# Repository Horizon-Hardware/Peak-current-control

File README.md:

# Peak-current-control
峰值电流控制PCB和代码

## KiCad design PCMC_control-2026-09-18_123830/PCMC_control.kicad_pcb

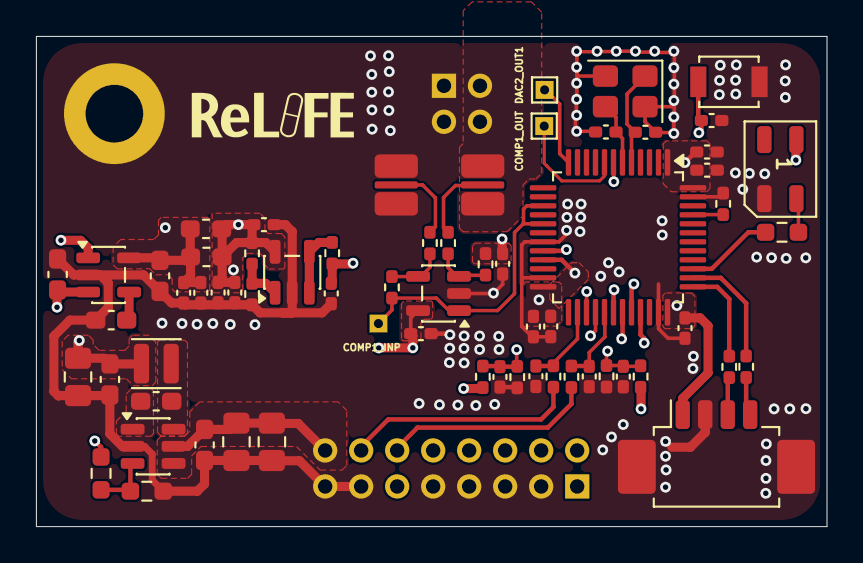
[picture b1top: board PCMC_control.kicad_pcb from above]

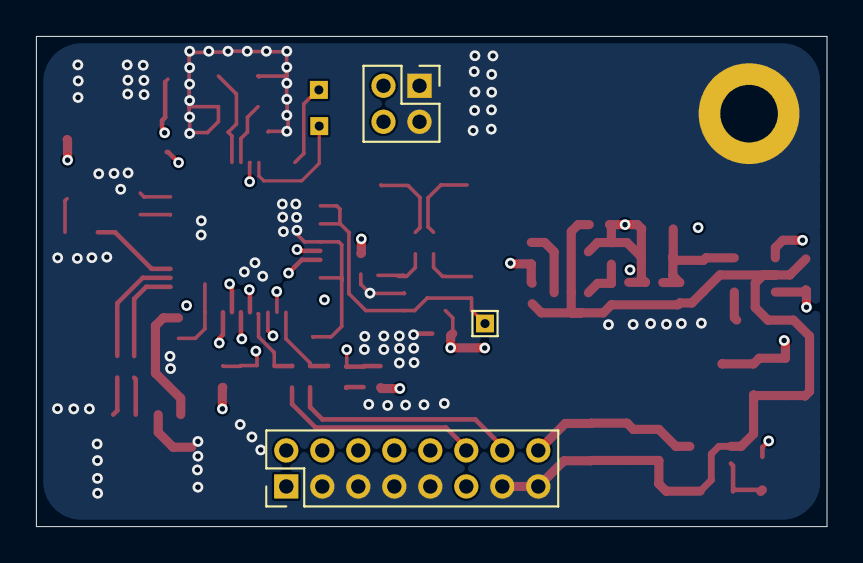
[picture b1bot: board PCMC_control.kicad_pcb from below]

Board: 4 copper layers, 43.9 x 27.2 mm, 67 parts (3 on the bottom side), 41 nets.

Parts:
C1, C4: 18p; C_0402_1005Metric_Pad0.74x0.62mm_HandSolder
C2, C13, C15: 100nf; C_0402_1005Metric_Pad0.74x0.62mm_HandSolder
C5, C6: 3n3; C_0402_1005Metric_Pad0.74x0.62mm_HandSolder
C7, C8, C9, C10, C11, C21, C24, C48: 100n; C_0402_1005Metric_Pad0.74x0.62mm_HandSolder
C16, C30: 3.3nf; C_0402_1005Metric_Pad0.74x0.62mm_HandSolder
C18, C22: 1u; C_0402_1005Metric_Pad0.74x0.62mm_HandSolder
C19, C31: 4.7u; C_0603_1608Metric_Pad1.08x0.95mm_HandSolder
C20, C23, C28: 100n; C_0603_1608Metric_Pad1.08x0.95mm_HandSolder
C25, C32, C33: 10u; C_0805_2012Metric_Pad1.18x1.45mm_HandSolder
C27: 10n; C_0603_1608Metric_Pad1.08x0.95mm_HandSolder
C35: 330P; C_0402_1005Metric_Pad0.74x0.62mm_HandSolder
D6: WS2812B; LED_WS2812B-Mini_PLCC4_3.5x3.5mm
H3: MountingHole_Pad; MountingHole_3.2mm_M3_DIN965_Pad
J2: Conn_01x04_MountingPin; Molex_PicoBlade_53261-0471_1x04-1MP_P1.25mm_Horizontal
J3: *; PinHeader_2x08_P2.00mm_Vertical
J10: Conn_02x02_Counter_Clockwise; PinHeader_2x02_P2.00mm_Vertical
L1, L4: GZ1608D601TF L0603; L_0603_1608Metric_Pad1.05x0.95mm_HandSolder
L2: 4.7u; L_APV_ANR252012
R1: 10K; R_0402_1005Metric_Pad0.72x0.64mm_HandSolder
R2, R3: 33kΩ; R_0402_1005Metric_Pad0.72x0.64mm_HandSolder
R4, R5, R35, R36: 2.2kΩ; R_0402_1005Metric_Pad0.72x0.64mm_HandSolder
R6, R8: 120; R_0402_1005Metric_Pad0.72x0.64mm_HandSolder
R15: 5mΩ; mΩ
R21: 2k; R_0603_1608Metric_Pad0.98x0.95mm_HandSolder
R22: 10k; R_0603_1608Metric_Pad0.98x0.95mm_HandSolder
R23, R24: 10k; R_0402_1005Metric_Pad0.72x0.64mm_HandSolder
R25: 10; R_0402_1005Metric_Pad0.72x0.64mm_HandSolder
R26, R28: 50K; R_0402_1005Metric_Pad0.72x0.64mm_HandSolder
R27: 120; R_0603_1608Metric_Pad0.98x0.95mm_HandSolder
R29, R30: 2.5K; R_0402_1005Metric_Pad0.72x0.64mm_HandSolder
RS3236_U1: RS3236; SOT-23-5
SW1: SW_Omron_B3FS; SW_SPST_B3U-1000P
TP1, TP3, TP6: TestPoint; TestPoint_THTPad_1.0x1.0mm_Drill0.5mm
U1: STM32G474CBTx; LQFP-48_7x7mm_P0.5mm
U3: SGM321YN5/TR; SOT-23-5
U6: TLV365DBV; SOT-23-5
U7: JW5026; SOT-23-6
Y1: Crystal_GND24; Crystal_SMD_3225-4Pin_3.2x2.5mm

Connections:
+1.65v: C15.2, C35.2, R25.2, R28.2
+3.3V: C7.1, C8.2, C9.2, C10.2, C11.2, C18.1, C21.1, C31.2, D6.1 (VDD), J2.1, J3.10, L1.1, L4.1, RS3236_U1.5 (OUT), U1.1 (VBAT), U1.21 (VDDA), U1.24 (VDD), U1.36 (VDD), U1.48 (VDD)
+5V: C19.1, C28.1, C32.1, L2.2, R22.1, RS3236_U1.1 (IN), RS3236_U1.3 (EN)
/ADC1_IN11: C30.1, R36.2, U1.26 (PB12)
/ADC2_IN15: C16.1, R35.2, U1.29 (ADC2_IN15)
/AGND+: R15.2, R30.2
/AGND-: R15.3, R29.2
/BOOT0: R1.2, U1.45 (PB8)
/COMP1_INP: R26.1, TP6.1 (1_1), U1.15 (PA7), U1.17 (PB1), U6.1
/COMP1_OUT: TP1.1 (1_1), U1.8 (PA0)
/DAC1_OUT1: TP3.1 (1_1), U1.12 (PA4)
/FB_5V: R21.1, R22.2, U7.3 (FB)
/FSBB_OUT: J3.1, R3.1
/HRTIM1_CHA1: J3.6, U1.30 (PA8)
/HRTIM1_CHA2: J3.8, U1.31 (PA9)
/HRTIM1_CHB1: J3.2, U1.32 (HRTIM1_CHB1)
/HRTIM1_CHB2: J3.4, U1.33 (HRTIM1_CHB2)
/I_BAT: J3.14, R36.1
/I_CHASSIS: J3.12, R35.1
/OPAMP2_VINP: C6.2, R3.2, R5.2, U1.28 (OPAMP2_VINP)
/OPAMP6_VINP: C5.2, R2.2, R4.2, U1.27 (PB13)
/PF0: C1.2, U1.5 (PF0), Y1.1
/PF1: C4.2, U1.6 (PF1), Y1.3
/PG10: C2.2, SW1.1, U1.7 (PG10)
/PGND_CAP: J10.3, J10.4, R15.4
/SWCLK: R8.2, U1.38 (SYS_JTCK-SWCLK)
/SWDIO: R6.2, U1.37 (SYS_JTMS-SWDIO)
/TIM2_CH1: R27.2, U1.39 (PA15)
/VREF+: C13.1, C22.1, C24.1, C48.2, J3.11, L1.2, L4.2, R24.1, U1.20 (VREF+), U3.5 (+VS), U6.5 (V+)
AGND: C1.1, C2.1, C4.1, C5.1, C6.1, C7.2, C8.1, C9.1, C10.1, C11.1, C13.2, C15.1, C16.2, C18.2, C19.2, C21.2, C22.2, C23.2, C24.2, C25.2, C27.2, C28.2, C30.2, C31.1, C32.2, C33.2, C35.1, C48.1, D6.3 (VSS), H3.1 (1_1), J2.2, J2.MP (MountPin), J3.3, J3.5, J3.7, J3.9, J3.13, J3.15, J10.1, J10.2, R1.1, R4.1, R5.1, R15.1, R21.2, R23.2, RS3236_U1.2 (GND), SW1.2, U1.19 (VSSA), U1.23 (VSS), U1.35 (VSS), U1.47 (VSS), U3.2 (-VS), U6.2 (V-), U7.2 (GND), Y1.2 (G), Y1.4 (G)
CHASSIS: C23.1, C25.1, C33.1, J3.16, R2.1, U7.4 (EN), U7.5 (VIN)
unnamed: D6.4 (DIN), R27.1
unnamed: J2.3, R6.1
unnamed: J2.4, R8.1
unnamed: C27.1, RS3236_U1.4 (BP)
unnamed: R23.1, R24.2, U3.1 (+IN)
unnamed: R25.1, U3.3 (-IN), U3.4 (OUT)
unnamed: R28.1, R29.1, U6.3 (+)
unnamed: R26.2, R30.1, U6.4 (-)
unnamed: C20.2, U7.1 (BST)
unnamed: C20.1, L2.1, U7.6 (SW)

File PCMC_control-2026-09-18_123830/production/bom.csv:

Designator,Footprint,Quantity,Value,LCSC Part #
"C1, C4",0402,2,18p,
"C10, C11, C21, C24, C48, C7, C8, C9",0402,8,100n,
"C13, C15, C2",0402,3,100nf,
"C16, C30",0402,2,3.3nf,
"C18, C22",0402,2,1u,
"C19, C31",0603,2,4.7u,
"C20, C23, C28",0603,3,100n,
"C25, C32, C33",0805,3,10u,
C27,0603,1,10n,
C35,0402,1,330P,
"C5, C6",0402,2,3n3,
,,,,
J10,PinHeader_2x02_P2.00mm_Vertical,1,Conn_02x02_Counter_Clockwise,
,,,,
J3,PinHeader_2x08_P2.00mm_Vertical,1,*,
"L1, L4",0603,2,GZ1608D601TF L0603,
L2,L_APV_ANR252012,1,4.7u,
"R1, R23, R24",0402,3,10K,
R15,2512,1,5mΩ,
"R2, R3",0402,2,33kΩ,
R21,0603,1,2k,
R22,0603,1,10k,
R25,0402,1,10,
"R26, R28",0402,2,50K,
R27,0603,1,120,
"R29, R30",0402,2,2.5K,
"R35, R36, R4, R5",0402,4,2.2kΩ,
"R6, R8",0402,2,120,
RS3236_U1,SOT-23-5,1,RS3236,
,,,,
,,,,
U1,LQFP-48_7x7mm_P0.5mm,1,STM32G474CBTx,
U3,SOT-23-5,1,SGM321YN5/TR,
U6,SOT-23-5,1,TLV365DBV,
U7,SOT-23-6,1,JW5026,

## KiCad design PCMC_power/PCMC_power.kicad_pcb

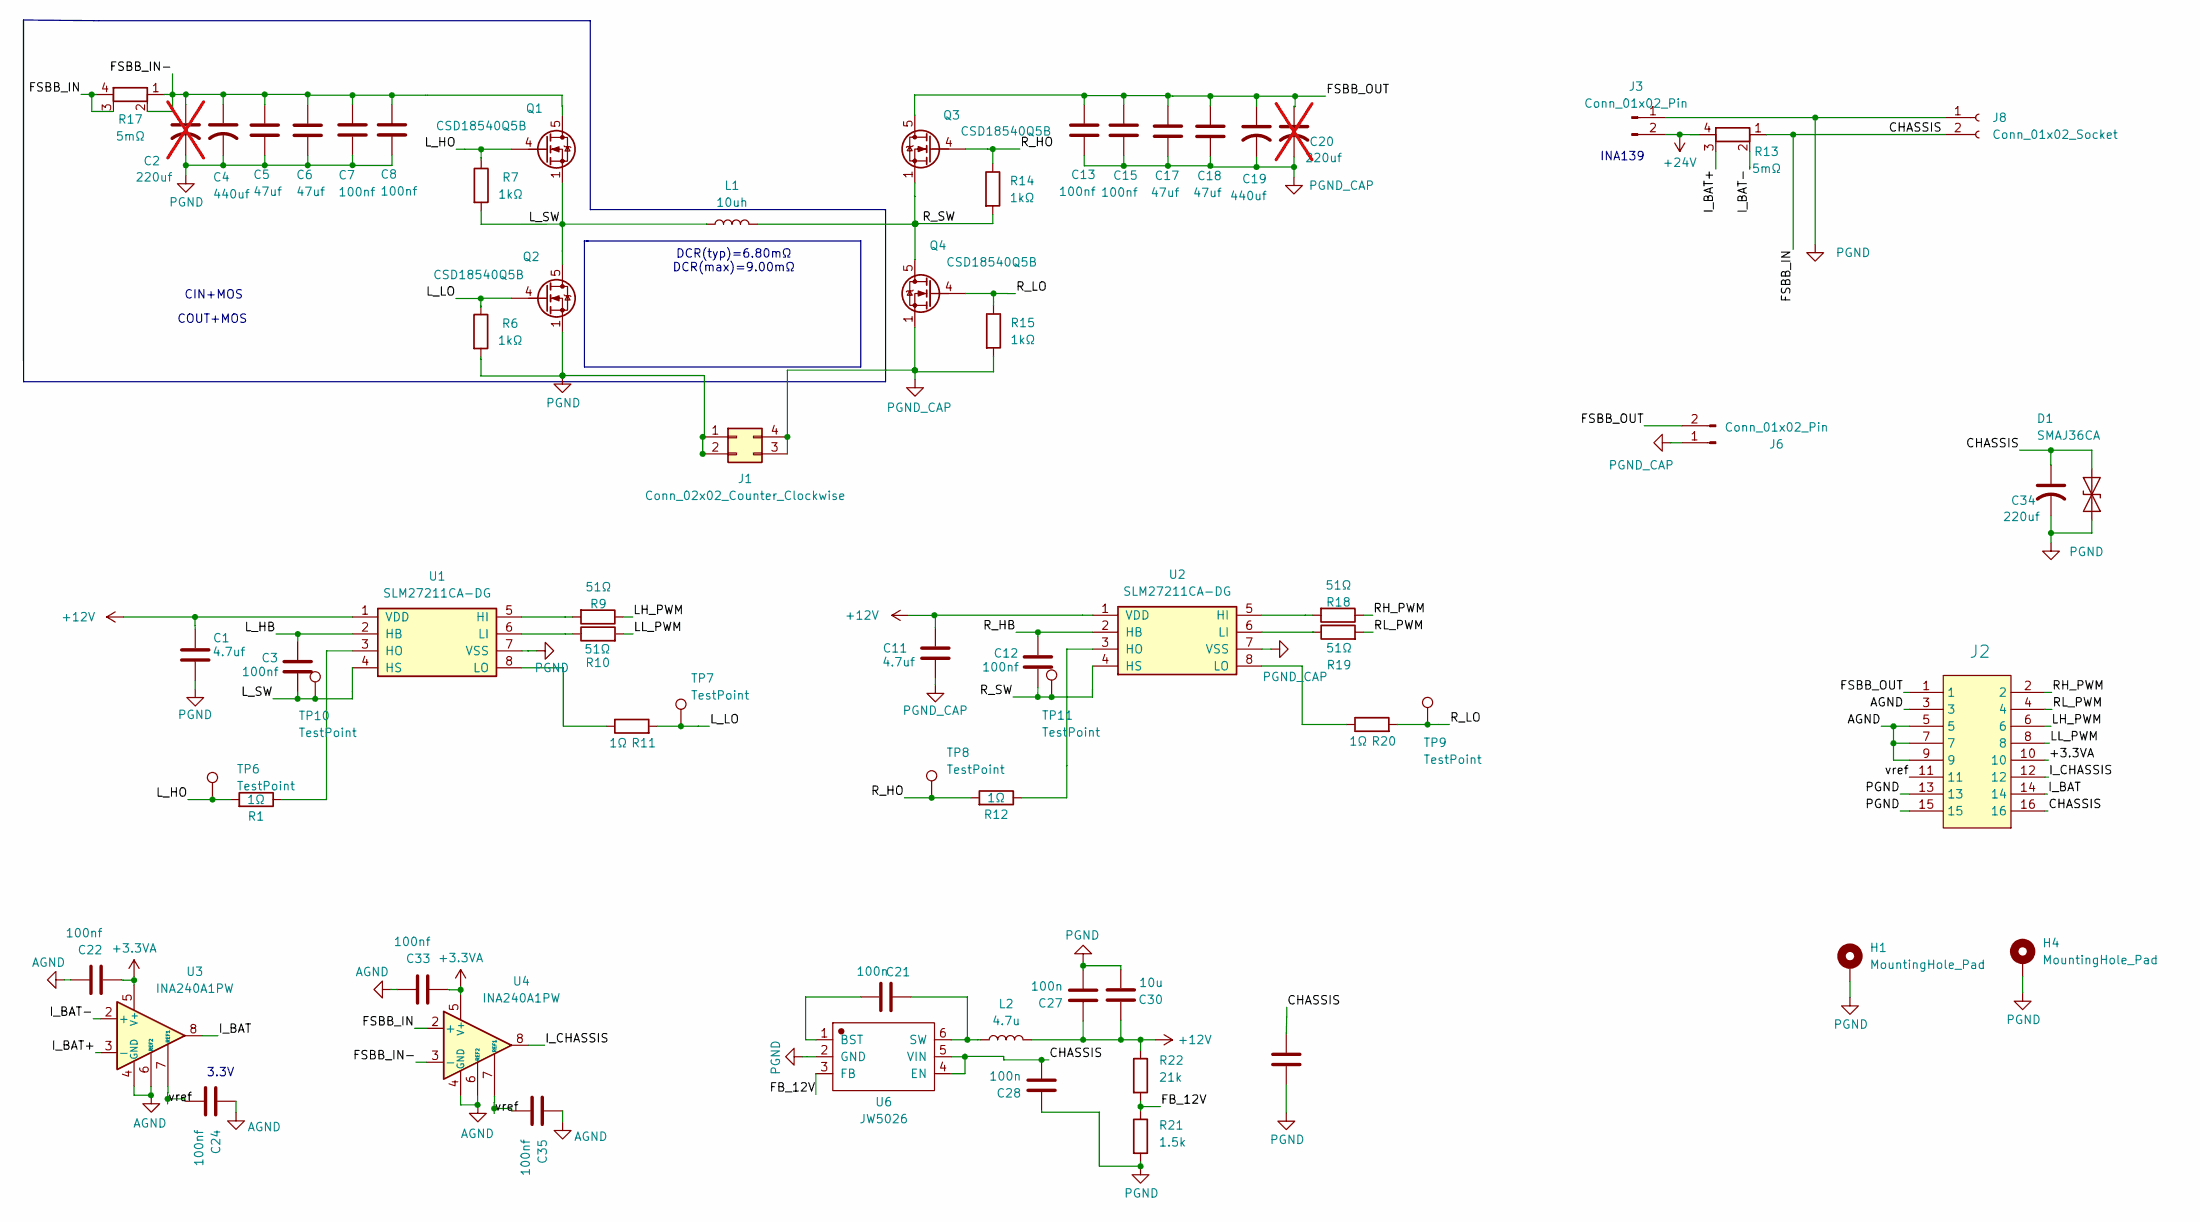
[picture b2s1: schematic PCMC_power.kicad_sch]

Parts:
C1, C11: 4.7uf; C_0603_1608Metric_Pad1.08x0.95mm_HandSolder
C2, C20: 220uf; C_Radial_D8.0mm_H7.0mm_P3.50mm; not fitted
C3, C7, C8, C12, C13, C15: 100nf; C_0805_2012Metric_Pad1.18x1.45mm_HandSolder
C4, C19: 440uf; CP_P3.5mm
C5, C6, C17, C18: 47uf; C_1210_3225Metric_Pad1.33x2.70mm_HandSolder
C21, C27, C28: 100n; C_0603_1608Metric_Pad1.08x0.95mm_HandSolder
C22, C24, C33, C35: 100nf; C_0402_1005Metric_Pad0.74x0.62mm_HandSolder
C30, C31: 10u; C_0805_2012Metric_Pad1.18x1.45mm_HandSolder
C34: 220uf; CP_P3.5mm
D1: SMAJ36CA; D_SMA
H1, H4: MountingHole_Pad; MountingHole_3.2mm_M3_DIN965_Pad
J1: Conn_02x02_Counter_Clockwise; PinHeader_2x02_P2.00mm_Vertical
J2: *; PinHeader_2x08_P2.00mm_Vertical
J3, J6: Conn_01x02_Pin; AMASS_XT30U-F_1x02_P5.0mm_Vertical
J8: Conn_01x02_Socket; AMASS_XT30U-F_1x02_P5.0mm_Vertical
L1: 10uh; L_Coilcraft_XAL1510-472
L2: 4.7u; L_APV_ANR252012
Q1, Q2, Q3, Q4: CSD18540Q5B; TDSON-8-1
R1, R11, R12, R20: 1Ω; R_0603_1608Metric_Pad0.98x0.95mm_HandSolder
R6, R7, R15: 1kΩ; R_0402_1005Metric_Pad0.72x0.64mm_HandSolder
R9, R10, R18, R19: 51Ω; R_0603_1608Metric_Pad0.98x0.95mm_HandSolder
R13, R17: 5mΩ; mΩ
R14: 1kΩ; R_0603_1608Metric_Pad0.98x0.95mm_HandSolder
R21: 1.5k; R_0603_1608Metric_Pad0.98x0.95mm_HandSolder
R22: 21k; R_0603_1608Metric_Pad0.98x0.95mm_HandSolder
TP6, TP7, TP8, TP9, TP10, TP11: TestPoint; TestPoint_THTPad_1.0x1.0mm_Drill0.5mm
U1, U2: SLM27211CA-DG; JEITA_SOIC-8_3.9x4.9mm_P1.27mm; MPN SLM27211CA-DG
U3, U4: INA240A1PW; TSSOP-8_4.4x3mm_P0.65mm
U6: JW5026; SOT-23-6

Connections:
+3.3VA: C22.2, C33.2, J2.10, U3.5 (V+), U4.5 (V+)
+12V: C1.1, C11.1, C27.1, C30.1, L2.2, R22.1, U1.1 (VDD), U2.1 (VDD)
+24V: J3.2, R13.4
/CHASSIS: C28.2, C31.1, C34.1, D1.2 (A2), J2.16, J8.2, R13.1, R17.3, R17.4, U4.2 (+), U6.4 (EN), U6.5 (VIN)
/FB_12V: R21.1, R22.2, U6.3 (FB)
/FSBB_IN-: C2.1, C4.1, C5.1, C6.1, C7.1, C8.1, Q1.5 (D), R17.1, R17.2, U4.3 (-)
/FSBB_OUT: C13.1, C15.1, C17.1, C18.1, C19.1, C20.1, J2.1, J6.2, Q3.5 (D)
/I_BAT: J2.14, U3.8
/I_BAT+: R13.3, U3.3 (-)
/I_BAT-: R13.2, U3.2 (+)
/I_CHASSIS: J2.12, U4.8
/LH_PWM: J2.6, R9.1
/LL_PWM: J2.8, R10.2
/L_HB: C3.1, U1.2 (HB)
/L_HO: Q1.4 (G), R1.2, R7.1, TP6.1 (1_1)
/L_LO: Q2.4 (G), R6.1, R11.2, TP7.1 (1_1)
/L_SW: C3.2, L1.1, Q1.1 (S), Q1.2 (S), Q1.3 (S), Q2.5 (D), R7.2, TP10.1 (1_1), U1.4 (HS)
/RH_PWM: J2.2, R18.1
/RL_PWM: J2.4, R19.2
/R_HB: C12.1, U2.2 (HB)
/R_HO: Q3.4 (G), R12.2, R14.1, TP8.1 (1_1)
/R_LO: Q4.4 (G), R15.1, R20.2, TP9.1 (1_1)
/R_SW: C12.2, L1.2, Q3.1 (S), Q3.2 (S), Q3.3 (S), Q4.5 (D), R14.2, TP11.1 (1_1), U2.4 (HS)
/vref: C24.2, C35.2, J2.11, U3.7 (REF1), U4.7 (REF1)
AGND: C22.1, C24.1, C33.1, C35.1, J2.3, J2.5, J2.7, J2.9, U3.1 (GND), U3.4 (GND), U3.6 (REF2), U4.1 (GND), U4.4 (GND), U4.6 (REF2)
unnamed: R9.2, U1.5 (HI)
unnamed: R1.1, U1.3 (HO)
unnamed: R10.1, U1.6 (LI)
unnamed: R11.1, U1.8 (LO)
unnamed: R18.2, U2.5 (HI)
unnamed: R12.1, U2.3 (HO)
unnamed: R19.1, U2.6 (LI)
unnamed: R20.1, U2.8 (LO)
unnamed: C21.2, U6.1 (BST)
unnamed: C21.1, L2.1, U6.6 (SW)
PGND: C1.2, C2.2, C4.2, C5.2, C6.2, C7.2, C8.2, C27.2, C28.1, C30.2, C31.2, C34.2, D1.1 (A1), H1.1 (1_1), H4.1 (1_1), J1.1, J1.2, J2.13, J2.15, J3.1, J8.1, Q2.1 (S), Q2.2 (S), Q2.3 (S), R6.2, R21.2, U1.7 (VSS), U6.2 (GND)
PGND_CAP: C11.2, C13.2, C15.2, C17.2, C18.2, C19.2, C20.2, J1.3, J1.4, J6.1, Q4.1 (S), Q4.2 (S), Q4.3 (S), R15.2, U2.7 (VSS)

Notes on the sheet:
DCR(typ)=6.80mΩ DCR(max)=9.00mΩ
COUT+MOS
3.3V
INA139
CIN+MOS

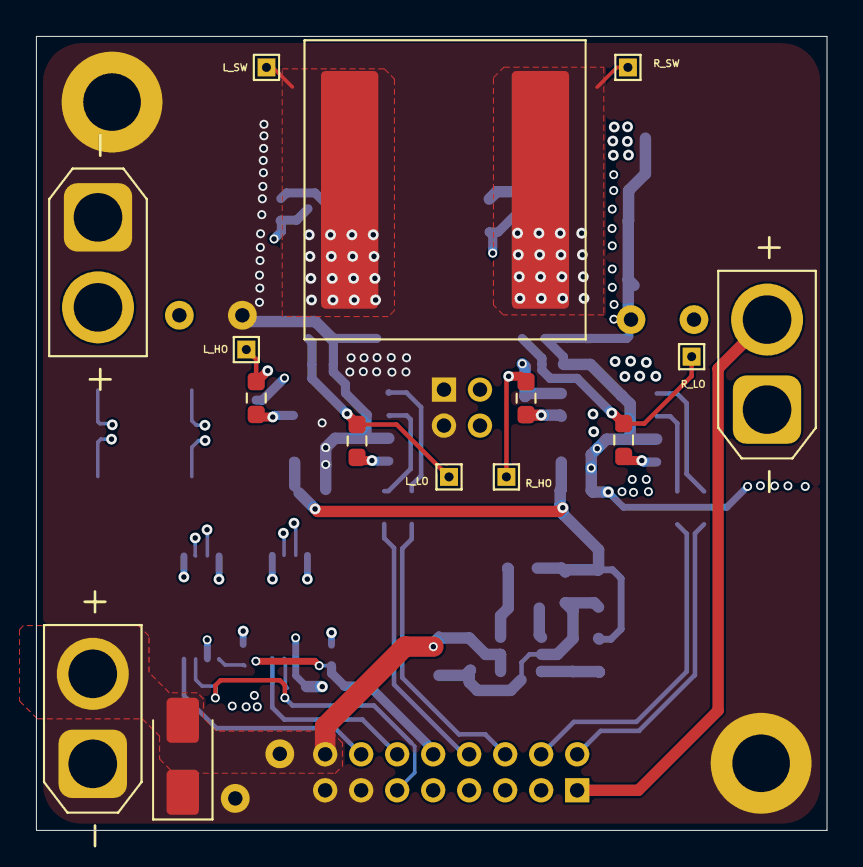
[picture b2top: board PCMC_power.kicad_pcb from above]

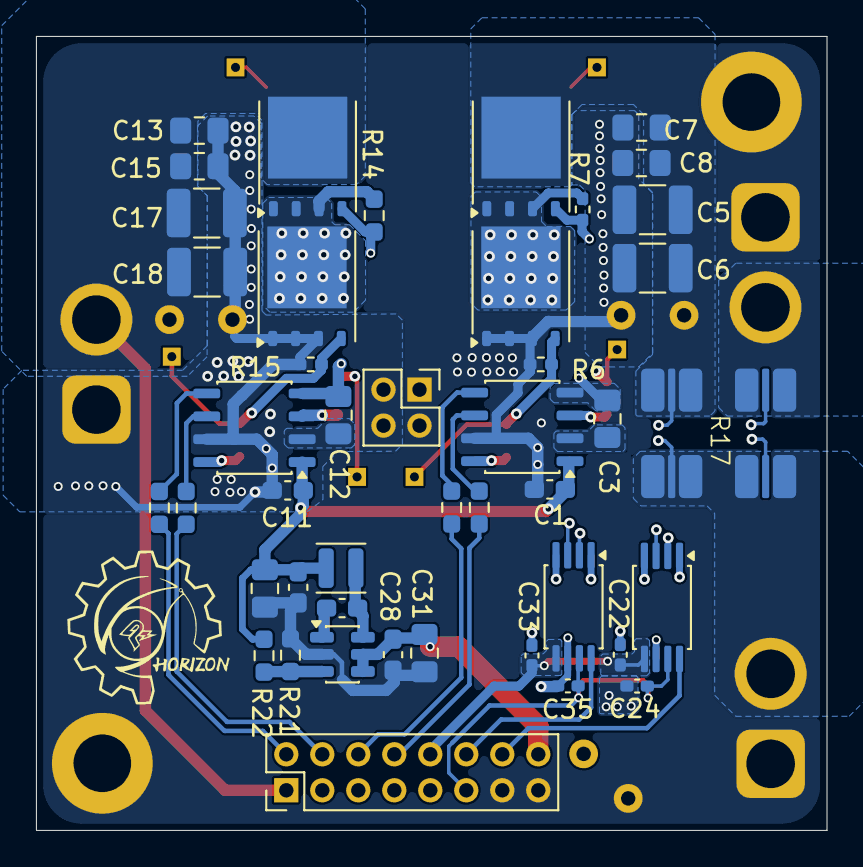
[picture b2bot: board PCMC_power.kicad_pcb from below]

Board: 4 copper layers, 43.9 x 44.1 mm, 65 parts (45 on the bottom side), 37 nets.

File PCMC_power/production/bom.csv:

Designator,Footprint,Quantity,Value,LCSC Part #
"C1, C11",0603,2,4.7uf,
"C12, C13, C15, C3, C7, C8",0805,6,100nf,
"C17, C18, C5, C6",1210,4,47uf,
"C19, C4",CP_P3.5mm,2,440uf,
"C21, C27, C28",0603,3,100n,
"C22, C24, C33, C35",0402,4,100nf,
"C30, C31",0805,2,10u,
,,,,
,,,,
J1,PinHeader_2x02_P2.00mm_Vertical,1,Conn_02x02_Counter_Clockwise,
J2,PinHeader_2x08_P2.00mm_Vertical,1,*,
,,,,
,,,,
L1,L_Coilcraft_XAL1510-472,1,10uh,
L2,L_APV_ANR252012,1,4.7u,
"Q1, Q2, Q3, Q4",TDSON-8-1,4,CSD18540Q5B,
"R1, R11, R12, R20",0603,4,1Ω,
"R10, R18, R19, R9",0603,4,51Ω,
"R13, R17",2512,2,5mΩ,
R14,0603,1,1kΩ,
"R15, R6, R7",0402,3,1kΩ,
R21,0603,1,1.5k,
R22,0603,1,21k,
,,,,
"U1, U2",JEITA_SOIC-8_3.9x4.9mm_P1.27mm,2,SLM27211CA-DG,SLM27211CA-DG
"U3, U4",TSSOP-8_4.4x3mm_P0.65mm,2,INA240A1PW,
U6,SOT-23-6,1,JW5026,

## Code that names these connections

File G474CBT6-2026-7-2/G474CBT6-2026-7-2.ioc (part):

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Mcu.Name=STM32G474C(B-C-E)Tx
Mcu.Package=LQFP48
Mcu.UserName=STM32G474CBTx
PA0.Mode=ExternalOutput
PA0.Signal=COMP1_OUT
PA10.Mode=Output_TB1TB2
PA10.Signal=HRTIM1_CHB1
PA11.Mode=Output_TB1TB2
PA11.Signal=HRTIM1_CHB2
PA13.Mode=Serial_Wire
PA13.Signal=SYS_JTMS-SWDIO
PA14.Mode=Serial_Wire
PA14.Signal=SYS_JTCK-SWCLK
PA15.Signal=S_TIM2_CH1
PA2.Mode=ExternalOutput
PA2.Signal=COMP2_OUT
PA4.Signal=COMP_DAC11_group
PA5.Signal=COMP_DAC12_group
PA6.Signal=SharedAnalog_PA6
PA7.Mode=INP
PA7.Signal=COMP2_INP
PA8.Mode=Output_TA1TA2
PA8.Signal=HRTIM1_CHA1
PA9.Mode=Output_TA1TA2
PA9.Signal=HRTIM1_CHA2
PB1.Mode=INP
PB1.Signal=COMP1_INP
PB11.Signal=SharedAnalog_PB11
PB12.Mode=IN11-Single-Ended
PB12.Signal=ADC1_IN11
PB13.Mode=Follower
PB13.Signal=OPAMP6_VINP
PB14.Mode=Follower
PB14.Signal=OPAMP2_VINP
PB15.Mode=IN15-Single-Ended
PB15.Signal=ADC2_IN15
PB6.Mode=Asynchronous
PB6.Signal=USART1_TX
PB7.Mode=Asynchronous
PB7.Signal=USART1_RX
PF0-OSC_IN.Mode=HSE-External-Oscillator
PF0-OSC_IN.Signal=RCC_OSC_IN
PF1-OSC_OUT.Mode=HSE-External-Oscillator
PF1-OSC_OUT.Signal=RCC_OSC_OUT
RCC.HSE_VALUE=12000000
RCC.SYSCLKFreq_VALUE=170000000
RCC.SYSCLKSource=RCC_SYSCLKSOURCE_PLLCLK
board=custom
